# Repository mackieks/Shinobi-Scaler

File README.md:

# Shinobi Scaler 1 (*OLD*) <picture> <source media="(prefers-color-scheme: dark)" srcset="images/logo_light.png">  </picture> 

Shinobi is a reimagined, miniaturized GBS8200 for portablizers. Like the original GBS8200, it can convert 240p and 480i RGBs to 480p/720p/960p/1080p VGA, making it perfect for connecting retro video game consoles to modern LCDs.

## Features
- [x] 47 x 57mm 2-layer PCB (designed in EAGLE)
- [x] Compatible with [rama's GBS-Control](https://github.com/ramapcsx2/gbs-control)
- [x] 240p/480i RGBs input; 480p/720p/960p/1080p RGBHV/VGA/YPbPr output
- [x] 0.1" PTHs for power and IO (can be mounted with pin headers on a carrier PCB)
- [x] TV5725 scaler IC and 64Mbit SDRAM from GBS8200
- [x] Integrated ESP8266 with PCB antenna
- [x] Integrated CH340C USB-Serial for programming
- [x] Integrated Si5351A clock generator
- [x] Draws 650mA @ 3.3V (2.15W) when scaling 240p to 480p
- [x] Power from 3.3V directly, or supply 4-15V to onboard high-current 3.3V regulator

## Gallery
Shinobi PCB

1Chip SNES RGBs upscaled to 640x480 VGA, displayed on ZJ050NA-08C LCD

## Ordering
Recommended fabrication specs:
- 1mm-thick 2-layer PCB
- ENIG finish
- Solderpaste stencil for top side highly recommended

**Note:** There are multiple revisions of the ESP-06 (ESP8266 module). Only the most recent revision is compatible with Shinobi. Make sure your ESP-06 has three "Wi-Fi lines" inside the A.I. Thinker logo circle, and that three of the four corner pads are *not* connected to GND. 

I maintain a [Mouser project](https://www.mouser.com/ProjectManager/ProjectDetail.aspx?AccessID=a0a4651c6a) with most of the BOM. Thanks to [biggestsonicfan](https://github.com/biggestsonicfan) for providing an equivalent [Digikey cart](https://digikey.com/short/t3m1vqz2)!

You will still need to source a TV5725, ESP-06, and CH340C elsewhere. Cheap GBS8200s are available from AliExpress, eBay, DHGate, and Amazon if you'd like to harvest the TV5725 and SDRAM from one. I get my [TV5725s](https://www.aliexpress.us/item/3256801105294792.html) and [CH340Cs](https://www.aliexpress.com/wholesale?&SearchText=ch340c) from AliExpress. ESP-06s can be obtained from [Eckstein-Shop](https://eckstein-shop.de/AI-Thinker-ESP8266-ESP-06-Serial-WIFI-Wireless-Remote-Control-Module).

**Update (11/3/22):** ESP-06s have been relisted on the AliExpress Keli-te Store.

**Update (1/25/23):** TPS621351RGXR is available for purchase on TI's website.

**Update (2/4/24):** TV5725 and ESP-06 links have been updated.

## Assembly
An ``ibom.html`` file exported via [InteractiveHtmlBom](https://github.com/openscopeproject/InteractiveHtmlBom) is included to facilitate assembly. Thanks, [biggestsonicfan](https://github.com/biggestsonicfan)!

As mentioned previously, you can harvest the TV5725 and SDRAM from a GBS-8200 if you'd like. Please note that previous advice to harvest the 0603 ferrite beads from the GBS-8200 is outdated. Use 220Ω @ 100MHz 0402 ferrite beads as called out in the BOM.

**Note:** There is an 0805 zero-ohm resistor (R19) in series with the output of the onboard 3.3V regulator. If you intend to power Shinobi from an external 3.3V supply, you can omit this resistor to avoid backfeeding the onboard 3.3V regulator. If you choose to remove the zero-ohm and/or U7 (TPS621351), the board will need to be powered with an external 3.3V supply during programming. 

## Programming
- Install [CH340 drivers](http://www.wch-ic.com/downloads/CH341SER_ZIP.html)
- Bridge the `prg` jumper with solder (or tweezers)
- Plug USB-C into Shinobi. **Note:** USB-C port works in both orientations on the latest board rev.
- Verify COM port (or your platform's equivalent) is enumerating
- Open GBS-Control release of your choice in Arduino IDE (these steps assume you have already installed requisite libraries, etc.)
- Set up Tools menu as shown, select CH340C port under Port menu, then program

- When programming is complete, unplug Shinobi, unbridge `prg`, and power back up to access GBS-Control Wi-Fi AP

## Undervolting

To undervolt Shinobi 1, do the following:
- [x] Replace R14 with an 0402 300k 1% resistor
- [x] Replace R15 with an 0402 787k 1% resistor
- [x] Replace U8 with LDL112PV15R 

This sets U7 to output 2.54V, and changes the DVDD rail to 1.5V. The LDO dropout is decreased from 1.5V (3.3->1.8) to only 1V (2.5->1.5). 

While this won't match Shinobi 2's power efficiency, it should still be a major improvement over a stock Shinobi 1.
  
## To-do
- [ ] Finish prototype enclosure and upload photos + MCAD files
- [ ] Run reliability tests for higher output resolutions (currently only 480P has been vetted)

## License
[Solderpad Hardware License v2.1](https://solderpad.org/licenses/SHL-2.1/)

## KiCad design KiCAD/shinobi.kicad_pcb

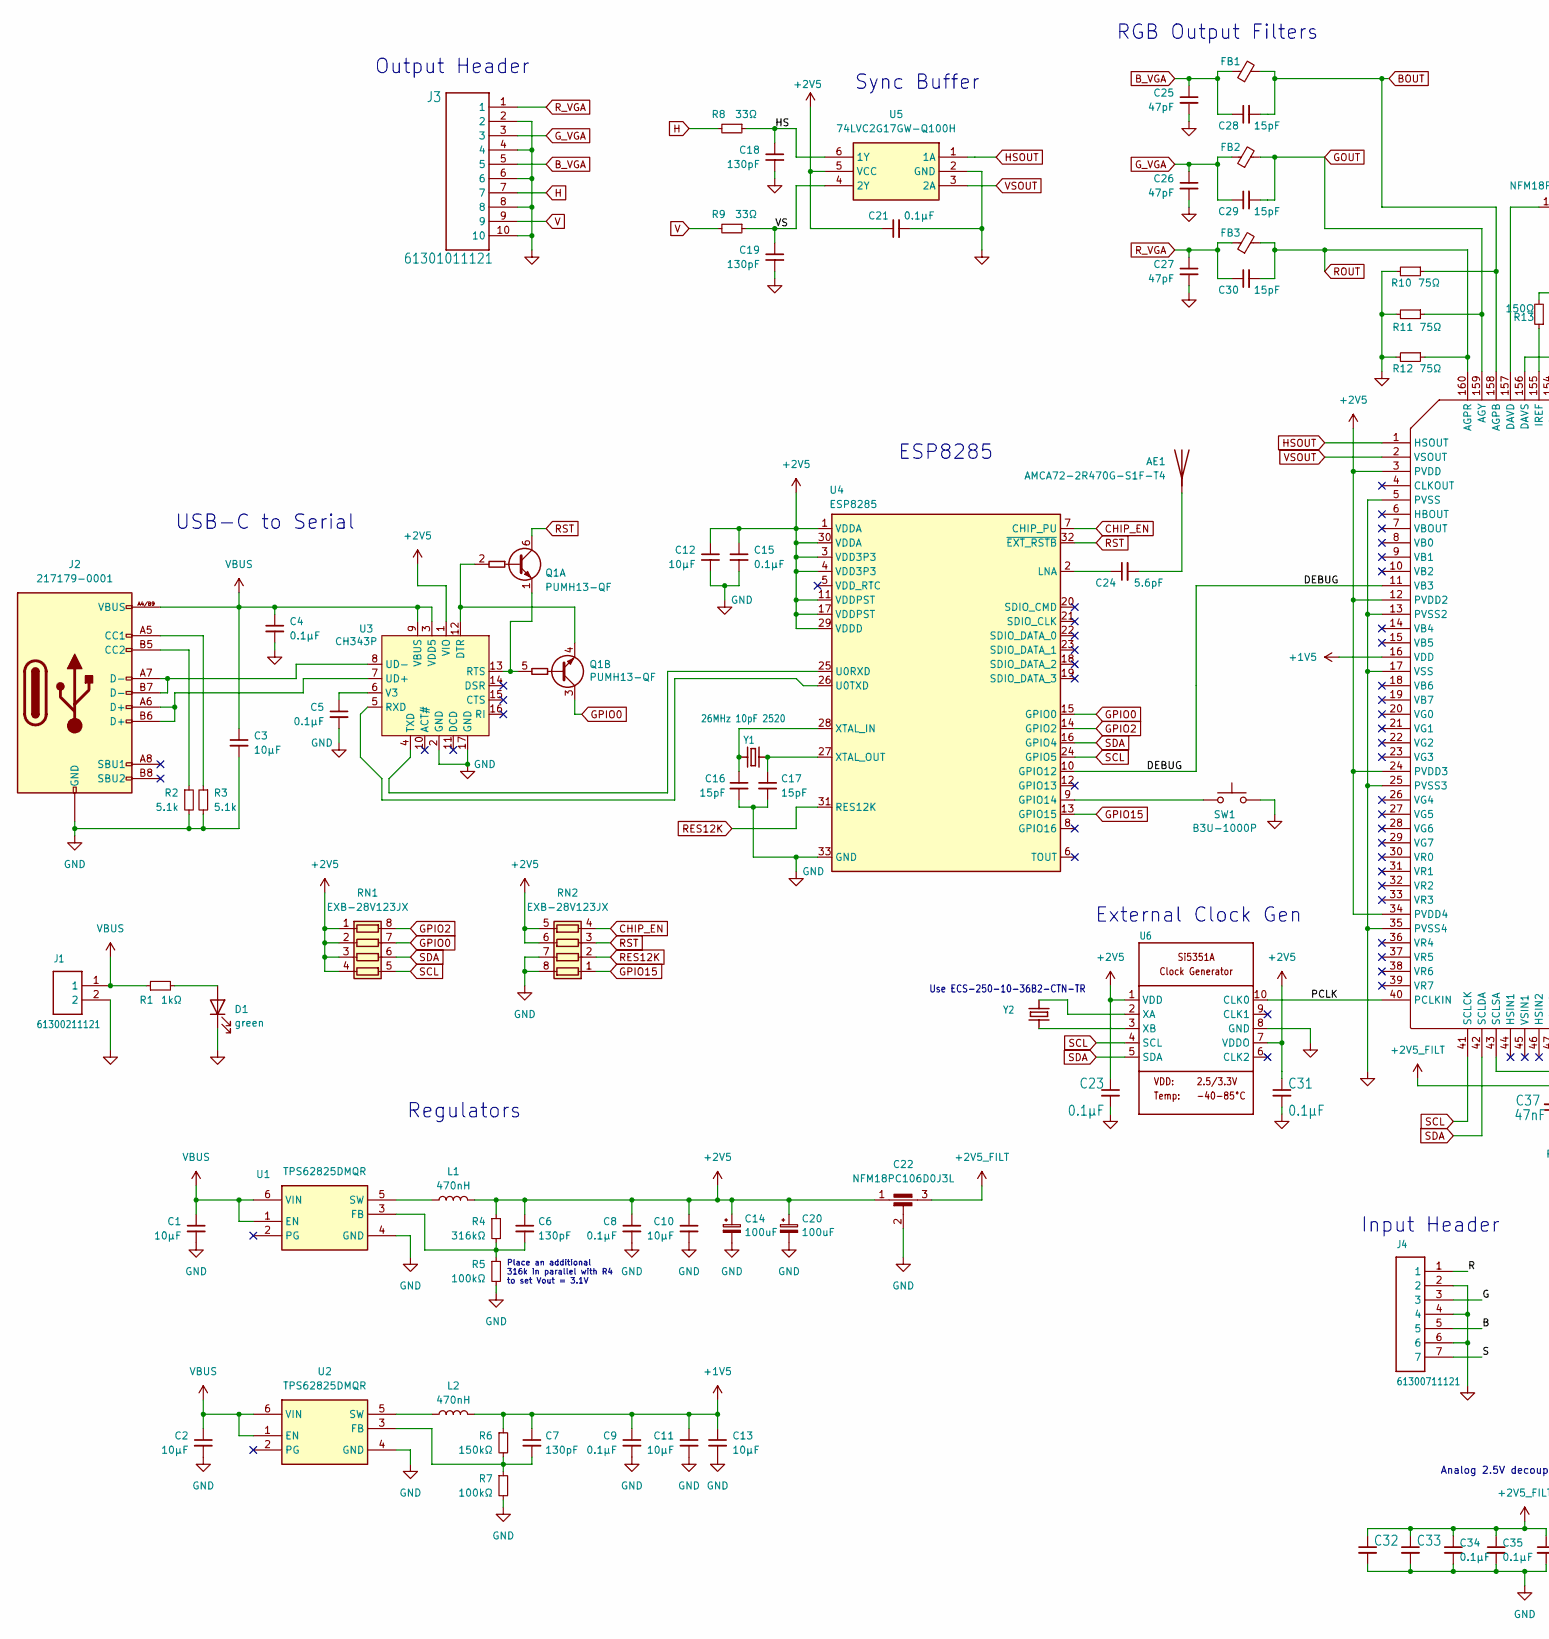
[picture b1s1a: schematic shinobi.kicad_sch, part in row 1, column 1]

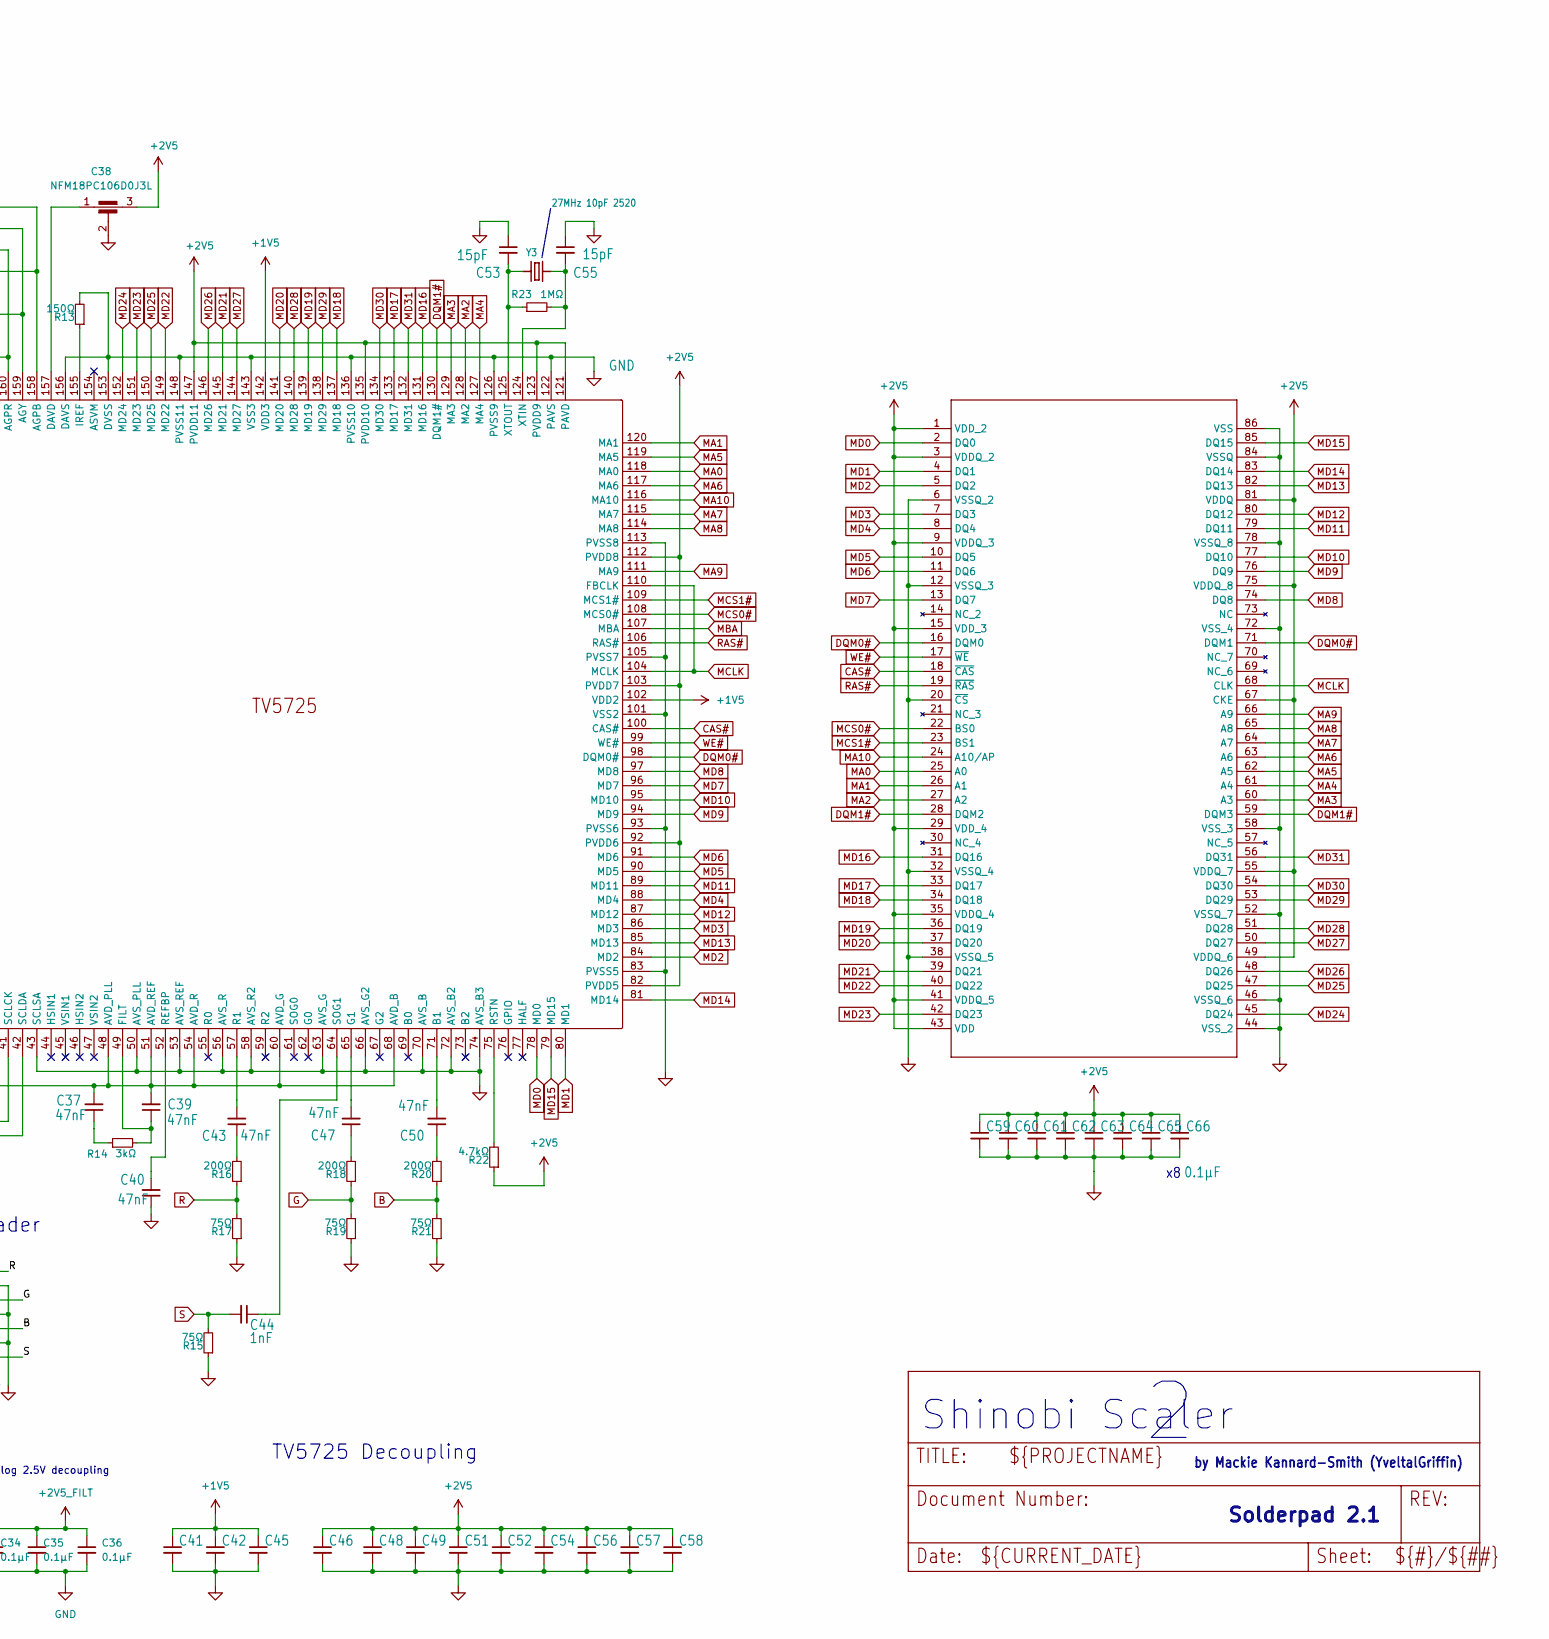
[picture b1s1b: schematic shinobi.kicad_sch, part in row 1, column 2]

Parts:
AE1: AMCA72-2R470G-S1F-T4; AMCA722R470GS1FT4
C1, C2: 10μF; C_0805_2012Metric
C3, C10, C11, C12, C13: 10μF; C_0603_1608Metric
C4, C5, C8, C9, C15, C21, C23, C31, C32, C33, C34, C35, C36, C41, C42, C45, C46, C48, C49, C51, C52, C54, C56, C57, C58, C59, C60, C61, C62, C63, C64, C65, C66: 0.1μF; C_0402_1005Metric
C6, C7, C18, C19: 130pF; C_0402_1005Metric
C14, C20: 100uF; CP_EIA-2012-12_Kemet-R
C16, C17, C28, C29, C30, C53, C55: 15pF; C_0402_1005Metric
C22, C38: NFM18PC106D0J3L
C24: 5.6pF; C_0402_1005Metric
C25, C26, C27: 47pF; C_0402_1005Metric
C37, C39, C40, C43, C47, C50: 47nF; C_0402_1005Metric
C44: 1nF; C_0402_1005Metric
D1: green; LED_0603_1608Metric
FB1, FB2, FB3: BLM15BD221SN1D; L_0402_1005Metric
J1: 61300211121
J2: 217179-0001; 2171790001_MOL_650876
J3: 61301011121
J4: 61300711121; 61300711121_11687645
L1, L2: 470nH; L_1008_2520Metric
Q1: PUMH13-QF; SOT-363_SC-70-6
R1: 1kΩ; R_0402_1005Metric
R2, R3: 5.1k; R_0402_1005Metric
R4: 316kΩ; R_0402_1005Metric
R5, R7: 100kΩ; R_0402_1005Metric
R6: 150kΩ; R_0402_1005Metric
R8, R9: 33Ω; R_0402_1005Metric
R10, R11, R12, R15, R17, R19, R21: 75Ω; R_0402_1005Metric
R13: 150Ω; R_0402_1005Metric
R14: 3kΩ; R_0402_1005Metric
R16, R18, R20: 200Ω; R_0402_1005Metric
R22: 4.7kΩ; R_0402_1005Metric
R23: 1MΩ; R_0402_1005Metric
RN1, RN2: EXB-28V123JX; R_Array_Convex_4x0402
SW1: B3U-1000P; SW_SPST_B3U-1000P
U1, U2: TPS62825DMQR; TPS62825DMQT; Mouser Part Number TPS62825DMQR
U3: CH343P; QFN-16-1EP_3x3mm_P0.5mm_EP1.7x1.7mm
U4: ESP8285; QFN-32-1EP_5x5mm_P0.5mm_EP3.45x3.45mm
U5: 74LVC2G17GW-Q100H; SOT65P210X110-6N; Mouser Part Number 771-74LVC2G17GWQ100H
U6: SI5351A; MSOP-10_3x3mm_P0.5mm
U7: TV5725; PQFP160_650876
U8: W9864G2JH-6; WIN_TSOP-86_WIN_650876
Y1: 26MHz 10pF 2520; Crystal_SMD_2520-4Pin_2.5x2.0mm
Y2: 25MHz 10pF 2520; Crystal_SMD_2520-4Pin_2.5x2.0mm
Y3: 27MHz 10pF 2520; Crystal_SMD_2520-4Pin_2.5x2.0mm

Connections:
+1V5: C7.1, C9.1, C11.1, C13.1, C41.1, C42.1, C45.1, L2.2, R6.1, U7.16 (VDD), U7.102 (VDD2), U7.142 (VDD3)
+2V5: C6.1, C8.1, C10.1, C12.1, C14.1, C15.1, C20.1, C21.1, C22.1, C23.1, C31.1, C38.3, C46.1, C48.1, C49.1, C51.1, C52.1, C54.1, C56.1, C57.1, C58.1, C59.1, C60.1, C61.1, C62.1, C63.1, C64.1, C65.1, C66.1, L1.2, R4.1, R22.1, RN1.1 (R1.1), RN1.2 (R2.1), RN1.3 (R3.1), RN1.4 (R4.1), RN2.5 (R4.2), RN2.6 (R3.2), U3.1 (VIO), U4.1 (VDDA), U4.3 (VDD3P3), U4.4 (VDD3P3), U4.11 (VDDPST), U4.17 (VDDPST), U4.29 (VDDD), U4.30 (VDDA), U5.5 (VCC), U6.1 (VDD), U6.7 (VDDO), U7.3 (PVDD), U7.12 (PVDD2), U7.24 (PVDD3), U7.34 (PVDD4), U7.82 (PVDD5), U7.92 (PVDD6), U7.103 (PVDD7), U7.112 (PVDD8), U7.121 (PAVD), U7.123 (PVDD9), U7.135 (PVDD10), U7.147 (PVDD11), U8.1 (VDD_2), U8.3 (VDDQ_2), U8.9 (VDDQ_3), U8.15 (VDD_3), U8.29 (VDD_4), U8.35 (VDDQ_4), U8.41 (VDDQ_5), U8.43 (VDD), U8.49 (VDDQ_6), U8.55 (VDDQ_7), U8.67 (CKE), U8.75 (VDDQ_8), U8.81 (VDDQ)
+2V5_FILT: C22.3, C32.1, C33.1, C34.1, C35.1, C36.1, C37.2, C39.2, U7.48 (AVD_PLL), U7.51 (AVD_REF), U7.54 (AVD_R), U7.60 (AVD_G), U7.68 (AVD_B)
/DEBUG: U4.10 (GPIO12), U7.11 (VB3)
/HS: C18.1, R8.1, U5.6 (1Y)
/PCLK: U6.10 (CLK0), U7.40 (PCLKIN)
/VS: C19.1, R9.1, U5.4 (2Y)
B: J4.5, R20.1, R21.2
BOUT: C28.2, FB1.2, R10.1, U7.158 (AGPB)
B_VGA: C25.1, C28.1, FB1.1, J3.5
CAS#: U7.100 (CAS#), U8.18 (~CAS)
CHIP_EN: RN2.4 (R4.1), U4.7 (CHIP_PU)
DQM0#: U7.98 (DQM0#), U8.16 (DQM0), U8.71 (DQM1)
DQM1#: U7.130 (DQM1#), U8.28 (DQM2), U8.59 (DQM3)
G: J4.3, R18.1, R19.2
GND: C1.2, C2.2, C3.2, C4.2, C5.2, C8.2, C9.2, C10.2, C11.2, C12.2, C13.2, C14.2, C15.2, C16.2, C17.2, C18.2, C19.2, C20.2, C21.2, C22.2, C22.4, C23.2, C25.2, C26.2, C27.2, C31.2, C32.2, C33.2, C34.2, C35.2, C36.2, C38.2, C38.4, C40.1, C41.2, C42.2, C45.2, C46.2, C48.2, C49.2, C51.2, C52.2, C53.1, C54.2, C55.1, C56.2, C57.2, C58.2, C59.2, C60.2, C61.2, C62.2, C63.2, C64.2, C65.2, C66.2, D1.1 (K), J1.2, J2.1 (GND), J2.2 (GND), J2.3 (GND), J2.4 (GND), J2.13 (GND), J2.14 (GND), J2.15 (GND), J2.16 (GND), J2.A1/B12 (GND_2), J2.B1/A12 (GND), J2.S_1_H1 (GND), J2.S_1_H2 (GND), J2.S_2_H1 (GND), J2.S_2_H2 (GND), J2.S_3_H1 (GND), J2.S_3_H2 (GND), J2.S_4_H1 (GND), J2.S_4_H2 (GND), J3.2, J3.4, J3.6, J3.8, J3.10, J4.2, J4.4, J4.6, R2.2, R3.2, R5.2, R7.2, R10.2, R11.2, R12.2, R13.2, R15.1, R17.1, R19.1, R21.1, RN2.7 (R2.2), RN2.8 (R1.2), SW1.2, U1.4 (GND), U2.4 (GND), U3.2 (GND), U3.17 (GND), U4.33 (GND), U5.2 (GND), U6.8 (GND), U7.5 (PVSS), U7.13 (PVSS2), U7.17 (VSS), U7.25 (PVSS3), U7.35 (PVSS4), U7.43 (SCLSA), U7.50 (AVS_PLL), U7.53 (AVS_REF), U7.56 (AVS_R), U7.58 (AVS_R2), U7.63 (AVS_G), U7.66 (AVS_G2), U7.70 (AVS_B), U7.72 (AVS_B2), U7.74 (AVS_B3), U7.83 (PVSS5), U7.93 (PVSS6), U7.101 (VSS2), U7.105 (PVSS7), U7.113 (PVSS8), U7.122 (PAVS), U7.126 (PVSS9), U7.136 (PVSS10), U7.143 (VSS3), U7.148 (PVSS11), U7.153 (DVSS), U7.156 (DAVS), U8.6 (VSSQ_2), U8.12 (VSSQ_3), U8.20 (~CS), U8.32 (VSSQ_4), U8.38 (VSSQ_5), U8.44 (VSS_2), U8.46 (VSSQ_6), U8.52 (VSSQ_7), U8.58 (VSS_3), U8.72 (VSS_4), U8.78 (VSSQ_8), U8.84 (VSSQ), U8.86 (VSS)
GOUT: C29.2, FB2.2, R11.1, U7.159 (AGY)
GPIO0: Q1.3 (C2), RN1.7 (R2.2), U4.15 (GPIO0)
GPIO2: RN1.8 (R1.2), U4.14 (GPIO2)
GPIO15: RN2.1 (R1.1), U4.13 (GPIO15)
G_VGA: C26.1, C29.1, FB2.1, J3.3
H: J3.7, R8.2
HSOUT: U5.1 (1A), U7.1 (HSOUT)
MA0: U7.118 (MA0), U8.25 (A0)
MA1: U7.120 (MA1), U8.26 (A1)
MA2: U7.128 (MA2), U8.27 (A2)
MA3: U7.129 (MA3), U8.60 (A3)
MA4: U7.127 (MA4), U8.61 (A4)
MA5: U7.119 (MA5), U8.62 (A5)
MA6: U7.117 (MA6), U8.63 (A6)
MA7: U7.115 (MA7), U8.64 (A7)
MA8: U7.114 (MA8), U8.65 (A8)
MA9: U7.111 (MA9), U8.66 (A9)
MA10: U7.116 (MA10), U8.24 (A10/AP)
MBA: U7.107 (MBA)
MCLK: U7.104 (MCLK), U7.110 (FBCLK), U8.68 (CLK)
MCS0#: U7.108 (MCS0#), U8.22 (BS0)
MCS1#: U7.109 (MCS1#), U8.23 (BS1)
MD0: U7.78 (MD0), U8.2 (DQ0)
MD1: U7.80 (MD1), U8.4 (DQ1)
MD2: U7.84 (MD2), U8.5 (DQ2)
MD3: U7.86 (MD3), U8.7 (DQ3)
MD4: U7.88 (MD4), U8.8 (DQ4)
MD5: U7.90 (MD5), U8.10 (DQ5)
MD6: U7.91 (MD6), U8.11 (DQ6)
MD7: U7.96 (MD7), U8.13 (DQ7)
MD8: U7.97 (MD8), U8.74 (DQ8)
MD9: U7.94 (MD9), U8.76 (DQ9)
MD10: U7.95 (MD10), U8.77 (DQ10)
MD11: U7.89 (MD11), U8.79 (DQ11)
MD12: U7.87 (MD12), U8.80 (DQ12)
MD13: U7.85 (MD13), U8.82 (DQ13)
MD14: U7.81 (MD14), U8.83 (DQ14)
MD15: U7.79 (MD15), U8.85 (DQ15)
MD16: U7.131 (MD16), U8.31 (DQ16)
MD17: U7.133 (MD17), U8.33 (DQ17)
MD18: U7.137 (MD18), U8.34 (DQ18)
MD19: U7.139 (MD19), U8.36 (DQ19)
MD20: U7.141 (MD20), U8.37 (DQ20)
MD21: U7.145 (MD21), U8.39 (DQ21)
MD22: U7.149 (MD22), U8.40 (DQ22)
MD23: U7.151 (MD23), U8.42 (DQ23)
MD24: U7.152 (MD24), U8.45 (DQ24)
MD25: U7.150 (MD25), U8.47 (DQ25)
MD26: U7.146 (MD26), U8.48 (DQ26)
MD27: U7.144 (MD27), U8.50 (DQ27)
MD28: U7.140 (MD28), U8.51 (DQ28)
MD29: U7.138 (MD29), U8.53 (DQ29)
MD30: U7.134 (MD30), U8.54 (DQ30)
MD31: U7.132 (MD31), U8.56 (DQ31)
unnamed: AE1.1 (A), C24.2
unnamed: C37.1, R14.1
unnamed: C43.1, R16.2
unnamed: C47.1, R18.2
unnamed: C50.1, R20.2
unnamed: D1.2 (A), R1.2
unnamed: J2.A5 (CC1), R3.1
unnamed: J2.B5 (CC2), R2.1
unnamed: Q1.2 (B1), Q1.4 (E2), U3.12 (DTR)
unnamed: Q1.1 (E1), Q1.5 (B2), U3.13 (RTS)
unnamed: C6.2, R4.2, R5.1, U1.3 (FB)
unnamed: L1.1, U1.5 (SW)
unnamed: C7.2, R6.2, R7.1, U2.3 (FB)
unnamed: L2.1, U2.5 (SW)
unnamed: U3.5 (RXD), U4.26 (U0TXD)
unnamed: U3.4 (TXD), U4.25 (U0RXD)
unnamed: J2.A6 (D+), J2.B6 (D+), U3.7 (UD+)
unnamed: J2.A7 (D-), J2.B7 (D-), U3.8 (UD-)
unnamed: C5.1, U3.6 (V3)
unnamed: SW1.1, U4.9 (GPIO14)
unnamed: C24.1, U4.2 (LNA)
unnamed: C16.1, U4.28 (XTAL_IN), Y1.1
unnamed: C17.1, U4.27 (XTAL_OUT), Y1.3 (2)
unnamed: U6.2 (XA), Y2.3 (2)
unnamed: U6.3 (XB), Y2.1
unnamed: C50.2, U7.71 (B1)
unnamed: C38.1, U7.157 (DAVD)
unnamed: C39.1, R14.2, U7.49 (FILT)
unnamed: C47.2, U7.65 (G1)
unnamed: R13.1, U7.155 (IREF)
unnamed: C43.2, U7.57 (R1)
unnamed: C40.2, U7.52 (REFBP)
unnamed: R22.2, U7.75 (RSTN)
unnamed: C44.1, U7.64 (SOG1)
unnamed: C55.2, R23.2, U7.124 (XTIN), Y3.3 (2)
unnamed: C53.2, R23.1, U7.125 (XTOUT), Y3.1
R: J4.1, R16.1, R17.2
RAS#: U7.106 (RAS#), U8.19 (~RAS)
RES12K: RN2.2 (R2.1), U4.31 (RES12K)
ROUT: C30.2, FB3.2, R12.1, U7.160 (AGPR)
RST: Q1.6 (C1), RN2.3 (R3.1), U4.32 (~EXT_RSTB)
R_VGA: C27.1, C30.1, FB3.1, J3.1
S: C44.2, J4.7, R15.2
SCL: RN1.5 (R4.2), U4.24 (GPIO5), U6.4 (SCL), U7.41 (SCLCK)
SDA: RN1.6 (R3.2), U4.16 (GPIO4), U6.5 (SDA), U7.42 (SCLDA)
V: J3.9, R9.2
VBUS: C1.1, C2.1, C3.1, C4.1, J1.1, J2.A4/B9 (VBUS), J2.B4/A9 (VBUS), R1.1, U1.1 (EN), U1.6 (VIN), U2.1 (EN), U2.6 (VIN), U3.3 (VDD5), U3.9 (VBUS)
VSOUT: U5.3 (2A), U7.2 (VSOUT)
WE#: U7.99 (WE#), U8.17 (~WE)

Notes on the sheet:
Shinobi Scaler
Analog 2.5V decoupling
Use ECS-250-10-36B2-CTN-TR
External Clock Gen
Solderpad 2.1
Input Header
USB-C to Serial
Place an additional 316k in parallel with R4 to set Vout = 3.1V
Output Header
Regulators
Sync Buffer
TV5725 Decoupling
by Mackie Kannard-Smith (YveltalGriffin)
ESP8285
RGB Output Filters

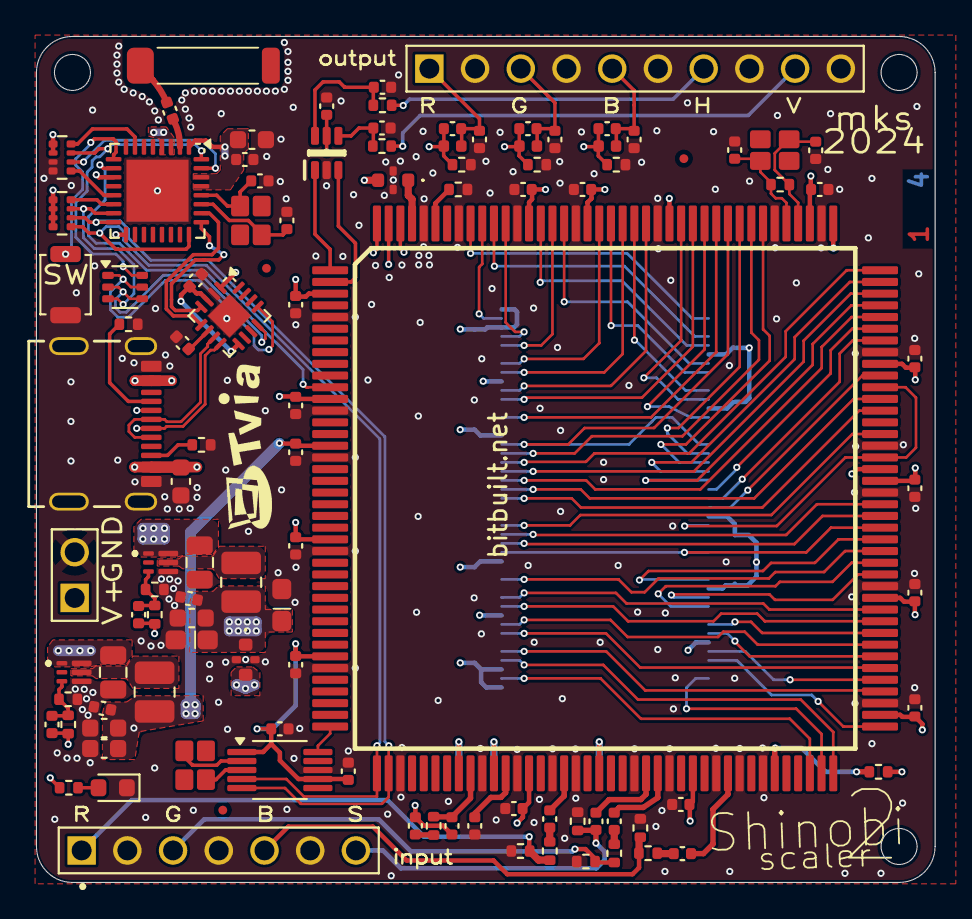
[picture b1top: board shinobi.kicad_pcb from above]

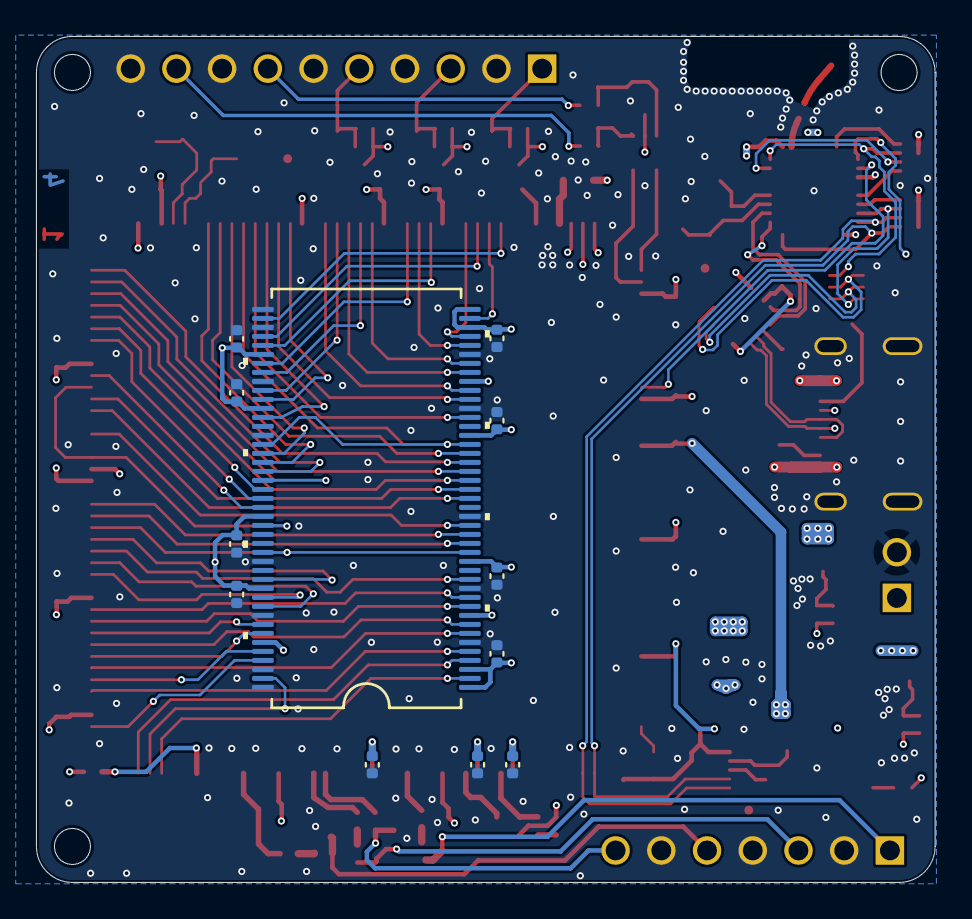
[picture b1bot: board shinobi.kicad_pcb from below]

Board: 4 copper layers, 49.9 x 47.0 mm, 115 parts (12 on the bottom side), 118 nets.

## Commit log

2022-10-24 Create LICENSE
2022-10-24 add source files
2022-10-24 update images
2022-10-25 update images, add eagle palette script
2022-10-25 add image and dxf
2022-10-25 fix ibom
2022-10-25 fix gerber issue, update schematic.png
2022-10-27 add demo photos
2022-12-05 Add MCAD (unfinished)
    -PCB STEP
    -Unfinished case file
2023-03-17 update board
2023-03-18 update brd
2023-07-21 update with correct ferrite beads
2023-07-25 Update LICENSE
2023-09-20 board update
    - minor tweak to cap placement (fixes soldermask aperture issue)
    -gerbers updated
    -iBOM updated
2024-01-23 update to solderpad license
2024-02-04 Update iBom and README
    Updates iBom to use InteractiveHtmlBom and edited README to include updated links to sourced components. Also updated my attribution to link to my github instead of twitter.
2024-07-17 WIP Shinobi 2
2024-07-18 shinobi2 routing
2024-07-18 Update PCB and BOM
2024-10-23 embed fonts, layout tweaks
2024-10-23 more minor layout tweaks
2024-10-23 tweak artwork
2024-10-28 small updates
2024-10-28 updating files
2024-10-28 update imgs
2024-10-28 add imgs
